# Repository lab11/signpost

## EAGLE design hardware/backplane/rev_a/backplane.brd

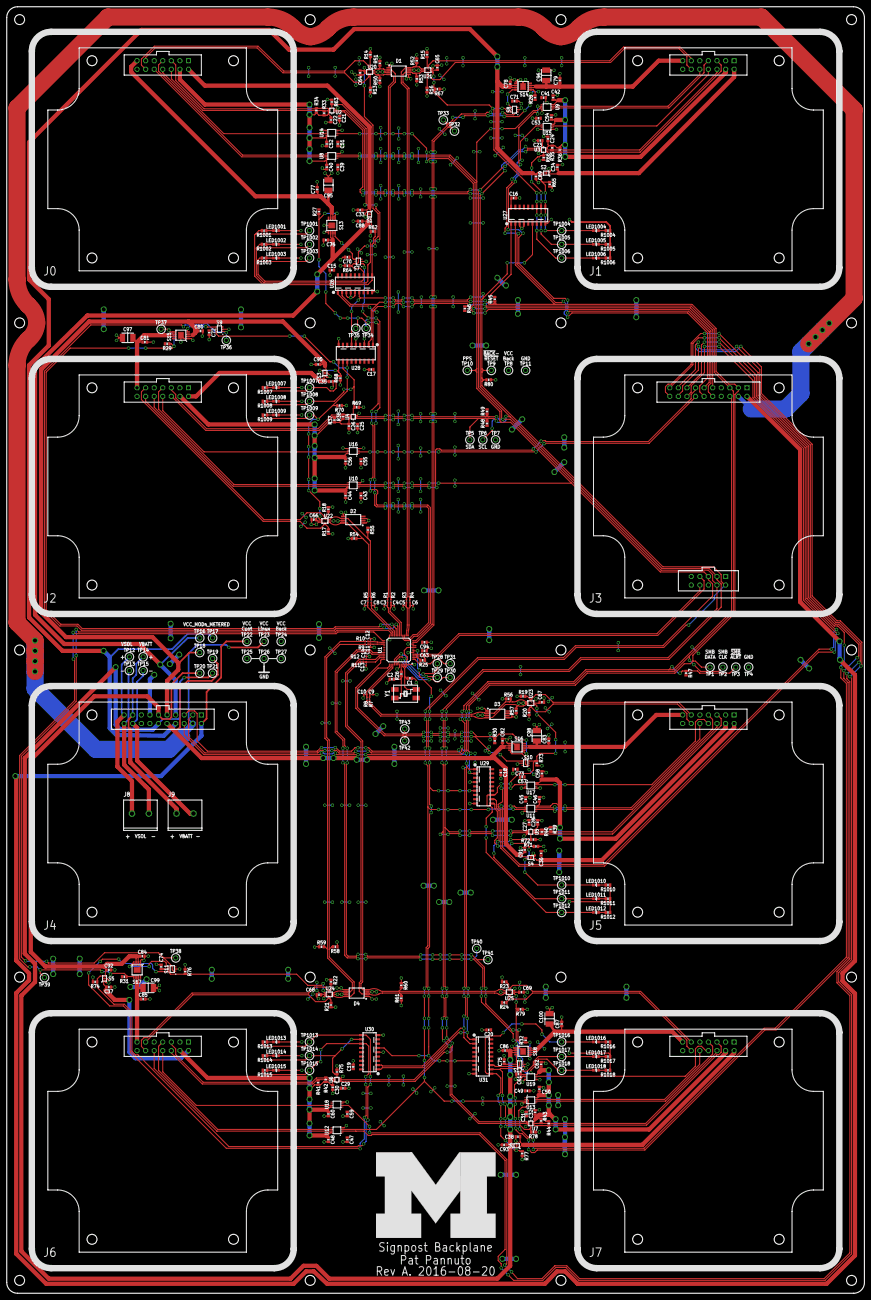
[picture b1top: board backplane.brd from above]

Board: 2 copper layers, 254.0 x 381.0 mm, 342 parts (0 on the bottom side), 193 nets.

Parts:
C1, C2: 22pF, 5% tol; 0603_CAP
C3, C4, C5, C6, C7, C8, C9, C10, C11, C12, C13, C14: 22pF; 0402_CAP
C15, C16, C17, C18, C19, C20, C21, C22, C23, C24, C25, C26, C27, C28, C29, C30, C31, C32, C33, C34, C35, C36, C37, C38, C39, C40, C41, C42, C43, C44, C45, C46, C47, C48, C49, C50, C51, C52, C53, C54, C55, C56, C57, C58, C59, C60, C61, C62, C63, C64, C65, C66, C67, C68, C69, C70, C71, C72, C73, C74, C75, C76, C77, C78, C79, C80, C81, C82, C83, C84, C85, C86, C87: 100nF; 0603_CAP
C88, C89, C90, C91, C92, C93, C94: 4.7uF; 0603_CAP
C95, C96, C97, C98, C99, C100: 150uF; 1210_CAP
D1, D2, D3, D4: SN75240-TSSOP; TSSOP-8
J0, J1, J2, J5, J6, J7: BACKPLANE_GENERIC_MODULE; BACKPLANE_MODULE_14PIN
J3: BACKPLANE_CONTROLLER_MODULE; BACKPLANE_MODULE_20PIN_10PIN
J4: BACKPLANE_POWER_MODULE; BACKPLANE_MODULE_20PIN
J8, J9: SCREW_TERMINAL; PHEONIX-1935161
LED1001, LED1002, LED1003, LED1004, LED1005, LED1006, LED1007, LED1008, LED1009, LED1010, LED1011, LED1012, LED1013, LED1014, LED1015, LED1016, LED1017, LED1018: LED0603; LED-0603
LOGO1: UMICH_SOLID_GIANT; UMICH_SOLID_1000MIL
R1, R2, R3, R4, R5, R6, R7, R8, R9, R10, R11, R12: 27Ω; 0402_RES-HIGH_SPEED
R13, R14, R15, R16, R17, R18, R19, R20, R21, R22, R23, R24: 50Ω; 0603-RES
R25, R26: 1.5kΩ; 0603-RES
R27, R28, R29, R30, R31, R32, R33, R34, R35, R36, R37, R38, R39, R40, R41, R42, R43, R44, R45, R46, R47, R48, R49: 10kΩ; 0603-RES
R50, R51, R52, R53, R54, R55, R56, R57, R58, R59, R60, R61: 15kΩ; 0603-RES
R62, R63, R64, R65, R66, R67, R68, R69, R70, R71, R72, R73, R74, R75, R76, R77, R78, R79, R80: 10MΩ; 0603-RES
R1001, R1002, R1003, R1004, R1005, R1006, R1007, R1008, R1009, R1010, R1011, R1012, R1013, R1014, R1015, R1016, R1017, R1018: 15Ω; 0603-RES
S1, S2, S3, S4, S5, S6: SIP3240X; TDFN4
S7, S8, S9, S10, S11, S12: NC7SZ157; SC70-6
S13, S14, S15, S16, S17, S18: AP2401MP; MSOP-8EP
TP1, TP2, TP3, TP4, TP5, TP6, TP7, TP8, TP9, TP10, TP11, TP12, TP13, TP14, TP15, TP16, TP17, TP18, TP19, TP20, TP21, TP22, TP23, TP24, TP25, TP26, TP27, TP28, TP29, TP30, TP31, TP32, TP33, TP34, TP35, TP36, TP37, TP38, TP39, TP40, TP41, TP42, TP43, TP1001, TP1002, TP1003, TP1004, TP1005, TP1006, TP1007, TP1008, TP1009, TP1010, TP1011, TP1012, TP1013, TP1014, TP1015, TP1016, TP1017, TP1018: TEST_POINT_0.040IN; TESTPOINT_0.040IN
U1: TUSB2077A; LQFP-48
U2, U3, U4, U5, U6, U7: FXMA2102; UMLP-8
U8, U9, U10, U11, U12, U13, U14, U15, U16, U17, U18, U19: SN74LVC2T45; VFSOP-8
U20, U21, U22, U23, U24, U25: TS3USB30E; UQFN-10
U26, U27, U28, U29, U30, U31: MCP23008; SOIC-18
Y1: ABMM

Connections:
!BACKPLANE_RESET: J3.22, R80.2, TP9.TESTPOINT, U1.6, U26.6, U27.6, U28.6, U29.6, U30.6, U31.6
!SMBALERT: J3.6, J4.6, R47.1, TP3.TESTPOINT
CONT_MOD0_IN: J3.9, U8.2
CONT_MOD0_OUT: J3.10, U14.2
CONT_MOD1_IN: J3.11, U9.2
CONT_MOD1_OUT: J3.12, U15.2
CONT_MOD2_IN: J3.13, U10.2
CONT_MOD2_OUT: J3.14, U16.2
CONT_MOD5_IN: J3.15, U11.2
CONT_MOD5_OUT: J3.16, U17.2
CONT_MOD6_IN: J3.17, U12.2
CONT_MOD6_OUT: J3.18, U18.2
CONT_MOD7_IN: J3.19, U13.2
CONT_MOD7_OUT: J3.20, U19.2
CONT_USB+: J3.27, R25.1, U1.3
CONT_USB-: J3.28, U1.4
GND: C1.1, C2.1, C3.2, C4.2, C5.2, C6.2, C7.2, C8.2, C9.2, C10.2, C11.2, C12.2, C13.2, C14.2, C15.2, C16.2, C17.2, C18.2, C19.2, C20.2, C21.2, C22.2, C23.2, C24.2, C25.2, C26.2, C27.2, C28.2, C29.2, C30.2, C31.2, C32.2, C33.2, C34.2, C35.2, C36.2, C37.2, C38.2, C39.2, C40.2, C41.2, C42.2, C43.2, C44.2, C45.2, C46.2, C47.2, C48.2, C49.2, C50.2, C51.2, C52.2, C53.2, C54.2, C55.2, C56.2, C57.2, C58.2, C59.2, C60.2, C61.2, C62.2, C63.1, C64.1, C65.1, C66.1, C67.1, C68.1, C69.1, C70.2, C71.2, C72.2, C73.2, C74.2, C75.2, C76.2, C77.2, C78.2, C79.2, C80.2, C81.2, C82.2, C83.2, C84.2, C85.2, C86.2, C87.2, C88.2, C89.2, C90.2, C91.2, C92.2, C93.2, C94.1, C95.2, C96.2, C97.2, C98.2, C99.2, C100.2, D1.1, D1.3, D1.5, D1.7, D2.1, D2.3, D2.5, D2.7, D3.1, D3.3, D3.5, D3.7, D4.1, D4.3, D4.5, D4.7, J0.1, J0.14, J1.1, J1.14, J2.1, J2.14, J3.1, J3.21, J4.1, J5.1, J5.14, J6.1, J6.14, J7.1, J7.14, LED1001.C, LED1002.C, LED1003.C, LED1007.C, LED1008.C, LED1009.C, LED1013.C, LED1014.C, LED1015.C, R13.2, R14.2, R15.2, R16.2, R17.2, R18.2, R19.2, R20.2, R21.2, R22.2, R23.2, R24.2, R50.1, R51.1, R52.1, R53.1, R54.1, R55.1, R56.1, R57.1, R58.1, R59.1, R60.1, R61.1, R62.1, R63.1, R64.1, R65.1, R66.1, R67.1, R68.1, R69.1, R70.1, R71.1, R72.1, R73.1, R74.1, R75.1, R76.1, R77.1, R78.1, R79.1, R80.1, R1004.1, R1005.1, R1006.1, R1010.1, R1011.1, R1012.1, R1016.1, R1017.1, R1018.1, S1.2, S1.PAD, S2.2, S2.PAD, S3.2, S3.PAD, S4.2, S4.PAD, S5.2, S5.PAD, S6.2, S6.PAD, S7.2, S8.2, S9.2, S10.2, S11.2, S12.2, S13.1, S13.PAD, S14.1, S14.PAD, S15.1, S15.PAD, S16.1, S16.PAD, S17.1, S17.PAD, S18.1, S18.PAD, TP4.TESTPOINT, TP7.TESTPOINT, TP11.TESTPOINT, TP25.TESTPOINT, TP26.TESTPOINT, TP27.TESTPOINT, U1.5, U1.10, U1.24, U1.43, U1.48, U2.4, U3.4, U4.4, U5.4, U6.4, U7.4, U8.4, U9.4, U10.4, U11.4, U12.4, U13.4, U14.4, U14.5, U15.4, U15.5, U16.4, U16.5, U17.4, U17.5, U18.4, U19.4, U19.5, U20.4, U20.10, U21.4, U21.10, U22.4, U22.10, U23.4, U23.10, U24.4, U24.10, U25.4, U25.10, U26.3, U26.4, U26.5, U26.9, U27.3, U27.4, U27.9, U28.3, U28.5, U28.9, U29.4, U29.9, U30.5, U30.9, U31.9
HUB_!OVRCUR1: R28.1, S14.5, TP33.TESTPOINT, U1.12
HUB_!OVRCUR2: R27.1, S13.5, TP35.TESTPOINT, U1.16
HUB_!OVRCUR3: R29.1, S15.5, TP37.TESTPOINT, U1.20
HUB_!OVRCUR4: R31.1, S17.5, TP39.TESTPOINT, U1.25
HUB_!OVRCUR6: R32.1, S18.5, TP41.TESTPOINT, U1.33
HUB_!OVRCUR7: R30.1, S16.5, TP43.TESTPOINT, U1.37
HUB_!PWRON1: S8.1, TP32.TESTPOINT, U1.11
HUB_!PWRON2: S7.1, TP34.TESTPOINT, U1.15
HUB_!PWRON3: S9.1, TP36.TESTPOINT, U1.19
HUB_!PWRON4: S11.1, TP38.TESTPOINT, U1.23
HUB_!PWRON6: S12.1, TP40.TESTPOINT, U1.32
HUB_!PWRON7: S10.1, TP42.TESTPOINT, U1.36
HUB_CFG: TP28.TESTPOINT, U1.40
HUB_DM1: C6.1, R4.1, U1.13
HUB_DM2: C4.1, R2.1, U1.17
HUB_DM3: C8.1, R6.1, U1.21
HUB_DM4: C12.1, R10.1, U1.26
HUB_DM6: C14.1, R12.1, U1.34
HUB_DM7: C10.1, R8.1, U1.38
HUB_DP1: C5.1, R3.1, U1.14
HUB_DP2: C3.1, R1.1, U1.18
HUB_DP3: C7.1, R5.1, U1.22
HUB_DP4: C11.1, R9.1, U1.27
HUB_DP6: C13.1, R11.1, U1.35
HUB_DP7: C9.1, R7.1, U1.39
HUB_PORTDIS: TP30.TESTPOINT, U1.42
HUB_PORTPWR: TP29.TESTPOINT, U1.41
MOD0_5V: C33.1, J0.2, S1.1
MOD0_5V_METERED: C76.1, C88.1, J4.7, S1.3, S13.2, S13.3, TP16.TESTPOINT
MOD0_D+_HUB-SW: D1.4, R1.2, R50.2, U20.3
MOD0_D-_HUB-SW: D1.2, R2.2, R51.2, U20.5
MOD0_IN: J0.10, U8.7
MOD0_ISO_I2C: R63.2, R1002.2, TP1002.TESTPOINT, U2.5, U26.11
MOD0_ISO_POWER: R62.2, R1001.2, S1.4, TP1001.TESTPOINT, U26.10
MOD0_ISO_USB: R64.2, R1003.2, S7.6, TP1003.TESTPOINT, U20.8, U26.12
MOD0_OUT: J0.8, U14.7
MOD0_PPS: J0.7, U8.6
MOD0_SCL: J0.5, R34.2, U2.6
MOD0_SDA: J0.6, R33.2, U2.7
MOD0_USB+: J0.11, U20.1
MOD0_USB-: J0.12, U20.7
MOD0_USB_!EN: S7.4, S13.4
MOD0_USB_VBUS: C77.1, C95.1, J0.13, S13.6, S13.7
MOD0_VCCIO: C22.1, C40.1, C52.1, J0.4, R33.1, R34.1, U2.8, U8.8, U14.8
MOD1_5V: C34.1, J1.2, S2.1
MOD1_5V_METERED: C78.1, C89.1, J4.8, S2.3, S14.2, S14.3, TP17.TESTPOINT
MOD1_D+_HUB-SW: D1.8, R3.2, R52.2, U21.3
MOD1_D-_HUB-SW: D1.6, R4.2, R53.2, U21.5
MOD1_IN: J1.10, U9.7
MOD1_ISO_I2C: LED1005.A, R66.2, TP1005.TESTPOINT, U3.5, U27.11
MOD1_ISO_POWER: LED1004.A, R65.2, S2.4, TP1004.TESTPOINT, U27.10
MOD1_ISO_USB: LED1006.A, R67.2, S8.6, TP1006.TESTPOINT, U21.8, U27.12
MOD1_OUT: J1.8, U15.7
MOD1_PPS: J1.7, U9.6
MOD1_SCL: J1.5, R36.2, U3.6
MOD1_SDA: J1.6, R35.2, U3.7
MOD1_USB+: J1.11, U21.1
MOD1_USB-: J1.12, U21.7
MOD1_USB_!EN: S8.4, S14.4
MOD1_USB_VBUS: C79.1, C96.1, J1.13, S14.6, S14.7
MOD1_VCCIO: C24.1, C42.1, C54.1, J1.4, R35.1, R36.1, U3.8, U9.8, U15.8
MOD2_5V: C35.1, J2.2, S3.1
MOD2_5V_METERED: C80.1, C90.1, J4.9, S3.3, S15.2, S15.3, TP18.TESTPOINT
MOD2_D+_HUB-SW: D2.8, R5.2, R54.2, U22.3
MOD2_D-_HUB-SW: D2.6, R6.2, R55.2, U22.5
MOD2_IN: J2.10, U10.7
MOD2_ISO_I2C: R69.2, R1008.2, TP1008.TESTPOINT, U4.5, U28.11
MOD2_ISO_POWER: R68.2, R1007.2, S3.4, TP1007.TESTPOINT, U28.10
MOD2_ISO_USB: R70.2, R1009.2, S9.6, TP1009.TESTPOINT, U22.8, U28.12
MOD2_OUT: J2.8, U16.7
MOD2_PPS: J2.7, U10.6
MOD2_SCL: J2.5, R38.2, U4.6
MOD2_SDA: J2.6, R37.2, U4.7
MOD2_USB+: J2.11, U22.1
MOD2_USB-: J2.12, U22.7
MOD2_USB_!EN: S9.4, S15.4
MOD2_USB_VBUS: C81.1, C97.1, J2.13, S15.6, S15.7
MOD2_VCCIO: C26.1, C44.1, C56.1, J2.4, R37.1, R38.1, U4.8, U10.8, U16.8
MOD5_5V: C36.1, J5.2, S4.1
MOD5_5V_METERED: C82.1, C91.1, J4.10, S4.3, S16.2, S16.3, TP19.TESTPOINT
MOD5_D+_HUB-SW: D3.2, R7.2, R56.2, U23.3
MOD5_D-_HUB-SW: D3.4, R8.2, R57.2, U23.5
MOD5_IN: J5.10, U11.7
MOD5_ISO_I2C: LED1011.A, R72.2, TP1011.TESTPOINT, U5.5, U29.11
MOD5_ISO_POWER: LED1010.A, R71.2, S4.4, TP1010.TESTPOINT, U29.10
MOD5_ISO_USB: LED1012.A, R73.2, S10.6, TP1012.TESTPOINT, U23.8, U29.12
MOD5_OUT: J5.8, U17.7
MOD5_PPS: J5.7, U11.6
MOD5_SCL: J5.5, R40.2, U5.6
MOD5_SDA: J5.6, R39.2, U5.7
MOD5_USB+: J5.11, U23.1
MOD5_USB-: J5.12, U23.7
MOD5_USB_!EN: S10.4, S16.4
MOD5_USB_VBUS: C83.1, C98.1, J5.13, S16.6, S16.7
MOD5_VCCIO: C28.1, C46.1, C58.1, J5.4, R39.1, R40.1, U5.8, U11.8, U17.8
MOD6_5V: C37.1, J6.2, S5.1
MOD6_5V_METERED: C84.1, C92.1, J4.11, S5.3, S17.2, S17.3, TP20.TESTPOINT
MOD6_D+_HUB-SW: D4.8, R9.2, R58.2, U24.3
MOD6_D-_HUB-SW: D4.6, R10.2, R59.2, U24.5
MOD6_IN: J6.10, U12.7
MOD6_ISO_I2C: R75.2, R1014.2, TP1014.TESTPOINT, U6.5, U30.11
MOD6_ISO_POWER: R74.2, R1013.2, S5.4, TP1013.TESTPOINT, U30.10
MOD6_ISO_USB: R76.2, R1015.2, S11.6, TP1015.TESTPOINT, U24.8, U30.12
MOD6_OUT: J6.8, U18.7
MOD6_PPS: J6.7, U12.6
MOD6_SCL: J6.5, R42.2, U6.6
MOD6_SDA: J6.6, R41.2, U6.7
MOD6_USB+: J6.11, U24.1
MOD6_USB-: J6.12, U24.7
MOD6_USB_!EN: S11.4, S17.4
MOD6_USB_VBUS: C85.1, C99.1, J6.13, S17.6, S17.7
MOD6_VCCIO: C30.1, C48.1, C60.1, J6.4, R41.1, R42.1, U6.8, U12.8, U18.8
MOD7_5V: C38.1, J7.2, S6.1
MOD7_5V_METERED: C86.1, C93.1, J4.12, S6.3, S18.2, S18.3, TP21.TESTPOINT
MOD7_D+_HUB-SW: D4.4, R11.2, R60.2, U25.3
MOD7_D-_HUB-SW: D4.2, R12.2, R61.2, U25.5
MOD7_IN: J7.10, U13.7
MOD7_ISO_I2C: LED1017.A, R78.2, TP1017.TESTPOINT, U7.5, U31.11
MOD7_ISO_POWER: LED1016.A, R77.2, S6.4, TP1016.TESTPOINT, U31.10
MOD7_ISO_USB: LED1018.A, R79.2, S12.6, TP1018.TESTPOINT, U25.8, U31.12
MOD7_OUT: J7.8, U19.7
MOD7_PPS: J7.7, U13.6
MOD7_SCL: J7.5, R44.2, U7.6
MOD7_SDA: J7.6, R43.2, U7.7
MOD7_USB+: J7.11, U25.1
MOD7_USB-: J7.12, U25.7
MOD7_USB_!EN: S12.4, S18.4
MOD7_USB_VBUS: C87.1, C100.1, J7.13, S18.6, S18.7
MOD7_VCCIO: C32.1, C50.1, C62.1, J7.4, R43.1, R44.1, U7.8, U13.8, U19.8
MOD_SCL: J3.24, R49.1, TP6.TESTPOINT, U2.3, U3.3, U4.3, U5.3, U6.3, U7.3
MOD_SDA: J3.23, R48.1, TP5.TESTPOINT, U2.2, U3.2, U4.2, U5.2, U6.2, U7.2
unnamed: LED1001.A, R1001.1
unnamed: LED1002.A, R1002.1
unnamed: LED1003.A, R1003.1
unnamed: LED1007.A, R1007.1
unnamed: LED1008.A, R1008.1
unnamed: LED1009.A, R1009.1
unnamed: LED1013.A, R1013.1
unnamed: LED1014.A, R1014.1
unnamed: LED1015.A, R1015.1
unnamed: LED1004.C, R1004.2
unnamed: LED1005.C, R1005.2
unnamed: R25.2, U1.2
unnamed: LED1006.C, R1006.2
unnamed: C2.2, R26.1, Y1.1
unnamed: LED1010.C, R1010.2
unnamed: LED1011.C, R1011.2
unnamed: R13.1, U20.2
unnamed: R24.1, U25.6
unnamed: R23.1, U25.2
unnamed: R22.1, U24.6
unnamed: R21.1, U24.2
unnamed: R20.1, U23.6
unnamed: R19.1, U23.2
unnamed: R17.1, U22.2
unnamed: R18.1, U22.6
unnamed: R16.1, U21.6
unnamed: R15.1, U21.2
unnamed: LED1012.C, R1012.2
unnamed: LED1016.C, R1016.2
unnamed: LED1017.C, R1017.2
unnamed: R14.1, U20.6
unnamed: LED1018.C, R1018.2
unnamed: C1.2, U1.45, Y1.3
unnamed: R26.2, U1.44
PPS: J3.25, TP10.TESTPOINT, U8.3, U9.3, U10.3, U11.3, U12.3, U13.3
SMBCLK: J3.5, J4.5, R46.1, TP2.TESTPOINT, U26.1, U27.1, U28.1, U29.1, U30.1, U31.1
SMBDATA: J3.3, J4.3, R45.1, TP1.TESTPOINT, U26.2, U27.2, U28.2, U29.2, U30.2, U31.2
USB_SUSPEND_STATUS: TP31.TESTPOINT, U1.1
VBATT+: J4.17, J9.1, TP14.TESTPOINT
VBATT-: J4.18, J9.2, TP15.TESTPOINT
VCC_BACKPLANE: C15.1, C16.1, C17.1, C18.1, C19.1, C20.1, C21.1, C23.1, C25.1, C27.1, C29.1, C31.1, C39.1, C41.1, C43.1, C45.1, C47.1, C49.1, C51.1, C53.1, C55.1, C57.1, C59.1, C61.1, C63.2, C64.2, C65.2, C66.2, C67.2, C68.2, C69.2, C70.1, C71.1, C72.1, C73.1, C74.1, C75.1, C94.2, J4.13, R27.2, R28.2, R29.2, R30.2, R31.2, R32.2, R45.2, R46.2, R47.2, R48.2, R49.2, S7.3, S7.5, S8.3, S8.5, S9.3, S9.5, S10.3, S10.5, S11.3, S11.5, S12.3, S12.5, TP8.TESTPOINT, TP24.TESTPOINT, U1.8, U1.9, U1.46, U1.47, U2.1, U3.1, U4.1, U5.1, U6.1, U7.1, U8.1, U8.5, U9.1, U9.5, U10.1, U10.5, U11.1, U11.5, U12.1, U12.5, U13.1, U13.5, U14.1, U15.1, U16.1, U17.1, U18.1, U19.1, U20.9, U21.9, U22.9, U23.9, U24.9, U25.9, U26.18, U27.5, U27.18, U28.4, U28.18, U29.3, U29.5, U29.18, U30.3, U30.4, U30.18, U31.3, U31.4, U31.5, U31.18
VCC_CONTROLLER: J3.2, J4.2, TP22.TESTPOINT
VCC_LINUX: J3.4, J4.4, TP23.TESTPOINT
VSOL+: J4.19, J8.1, TP12.TESTPOINT
VSOL-: J4.20, J8.2, TP13.TESTPOINT

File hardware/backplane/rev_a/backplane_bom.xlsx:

Qty | Value | Device | Package | Parts | Description | DIGIKEY
2 | 22pF, 5% tol | CAPACITOR0603_CAP | 0603_CAP | C1, C2 | 0402 Capacitor | 1276-1023-1-ND
12 | 22pF | CAPACITOR0402_CAP | 0402_CAP | C3, C4, C5, C6, C7, C8, C9, C10, C11, C12, C13, C14 | 0402 Capacitor | 490-5868-1-ND
73 | 100nF | CAPACITOR0603_CAP | 0603_CAP | C15, C16, C17, C18, C19, C20, C21, C22, C23, C24, C25, C26, C27, C28, C29, C30,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 | 0402 Capacitor | 490-1524-1-ND
7 | 4.7uF | CAPACITOR0603_CAP | 0603_CAP | C88, C89, C90, C91, C92, C93, C94 | 0402 Capacitor
6 | 150uF | CAPACITOR1210_CAP | 1210_CAP | C95, C96, C97, C98, C99, C100 | 0402 Capacitor | 1276-3367-1-ND
4 | SN75240-TSSOP | SN75240-TSSOP | TSSOP-8 | D1, D2, D3, D4 | TVS Diodes [suggested for TI USB Hub] (2 array) | 296-6596-1-ND
6 | BACKPLANE_GENERIC_MODULE | BACKPLANE_GENERIC_MODULE | BACKPLANE_MODULE_14PIN | J0, J1, J2, J5, J6, J7 | Signpost generic module recepticle | S9195-ND
1 | BACKPLANE_CONTROLLER_MODULE | BACKPLANE_CONTROLLER_MODULE | BACKPLANE_MODULE_20PIN_10PIN | J3 | Signpost controller recepticle | S9197-ND , S9194-ND
1 | BACKPLANE_POWER_MODULE | BACKPLANE_POWER_MODULE | BACKPLANE_MODULE_20PIN | J4 | Signpost power module recepticle | S9197-ND
2 | SCREW_TERMINAL | SCREW_TERMINAL | PHEONIX-1935161 | J8, J9 | PCB terminal block 5mm | 277-1667-ND
18 | LED0603 | LED0603 | LED-0603 | LED1001, LED1002, LED1003, LED1004, LED1005, LED1006, LED1007, LED1008, LED1009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 | LED
12 | 27 | RESISTOR0402_RES-HIGH_SPEED | 0402_RES-HIGH_SPEED | R1, R2, R3, R4, R5, R6, R7, R8, R9, R10, R11, R12 | Resistor
12 | 50 | RESISTOR0603_RES | 0603-RES | R13, R14, R15, R16, R17, R18, R19, R20, R21, R22, R23, R24 | Resistor
2 | 1.5k | RESISTOR0603_RES | 0603-RES | R25, R26 | Resistor
23 | 10k | RESISTOR0603_RES | 0603-RES | R27, R28, R29, R30, R31, R32, R33, R34, R35, R36, R37, R38, R39, R40, R41, R42,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 | Resistor
12 | 15k | RESISTOR0603_RES | 0603-RES | R50, R51, R52, R53, R54, R55, R56, R57, R58, R59, R60, R61 | Resistor
19 | 10M | RESISTOR0603_RES | 0603-RES | R62, R63, R64, R65, R66, R67, R68, R69, R70, R71, R72, R73, R74, R75, R76, R77,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 | Resistor
18 | 15 | RESISTOR0603_RES | 0603-RES | R1001, R1002, R1003, R1004, R1005, R1006, R1007, R1008, R1009, R1010, R1011, R1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 | Resistor
6 | SIP3240X | SIP3240X | TDFN4 | S1, S2, S3, S4, S5, S6 | High power (2.4 A) high-side switch | SIP32402ADNP-T1GE4CT-ND
6 | AP2401MP | AP2401MP | MSOP-8EP | S13, S14, S15, S16, S17, S18 | USB Power Switch | AP2401MP-13DICT-ND
6 | NC7SZ157 | NC7SZ157 | SC70-6 | S7, S8, S9, S10, S11, S12 | MUX | NC7SZ157P6XCT-ND
61 | TEST_POINT_0.040IN | TEST_POINT_0.040IN | TESTPOINT_0.040IN | TP1, TP2, TP3, TP4, TP5, TP6, TP7, TP8, TP9, TP10, TP11, TP12, TP13, TP14, TP15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 | 0.040in Test Point | 5001K-ND
1 | TUSB2077A | TUSB2077A | LQFP-48 | U1 | Full Speed USB Hub - 7 Port | 296-37871-1-ND
6 | FXMA2102 | FXMA2102 | UMLP-8 | U2, U3, U4, U5, U6, U7 | Dual Supply, 2-Bit Voltage Translator / Buffer / Repeater / Isolator for I2C | FXMA2102UMXCT-ND
6 | TS3USB30E | TS3USB30E | UQFN-10 | U20, U21, U22, U23, U24, U25 | USB Mux with OE control and ESD | 296-24684-1-ND
6 | MCP23008 | MCP23008 | SOIC-18 | U26, U27, U28, U29, U30, U31 | GPIO Extender via I2C - 8 Pin | MCP23008T-E/SOCT-ND
12 | SN74LVC2T45 | SN74LVC2T45 | VFSOP-8 | U8, U9, U10, U11, U12, U13, U14, U15, U16, U17, U18, U19 | Bidirectional Buffer / Level Converter 2 Circuits | 296-17014-1-ND
1 | ABMM | ABMM | ABMM | Y1 | Low-Profile SMD crystal | 535-10156-1-ND

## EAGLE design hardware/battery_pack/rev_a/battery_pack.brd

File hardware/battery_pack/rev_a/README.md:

This is a first pass at a signpost battery pack.

It will be simple. Several li-ion cells with a protection IC.

I would like to have OV/UV/OT/UT protection.

In the future we may consider adding active temperature
compensation (such as a pcb heater under the batteries),
but this design will not include that feature.

I am planning on using the TIbq77904. This will protect
series li-ion cells. It will not balance them (and could 
therefore not get optimal pack lifetime) but it is a 
relatively simple first pass.

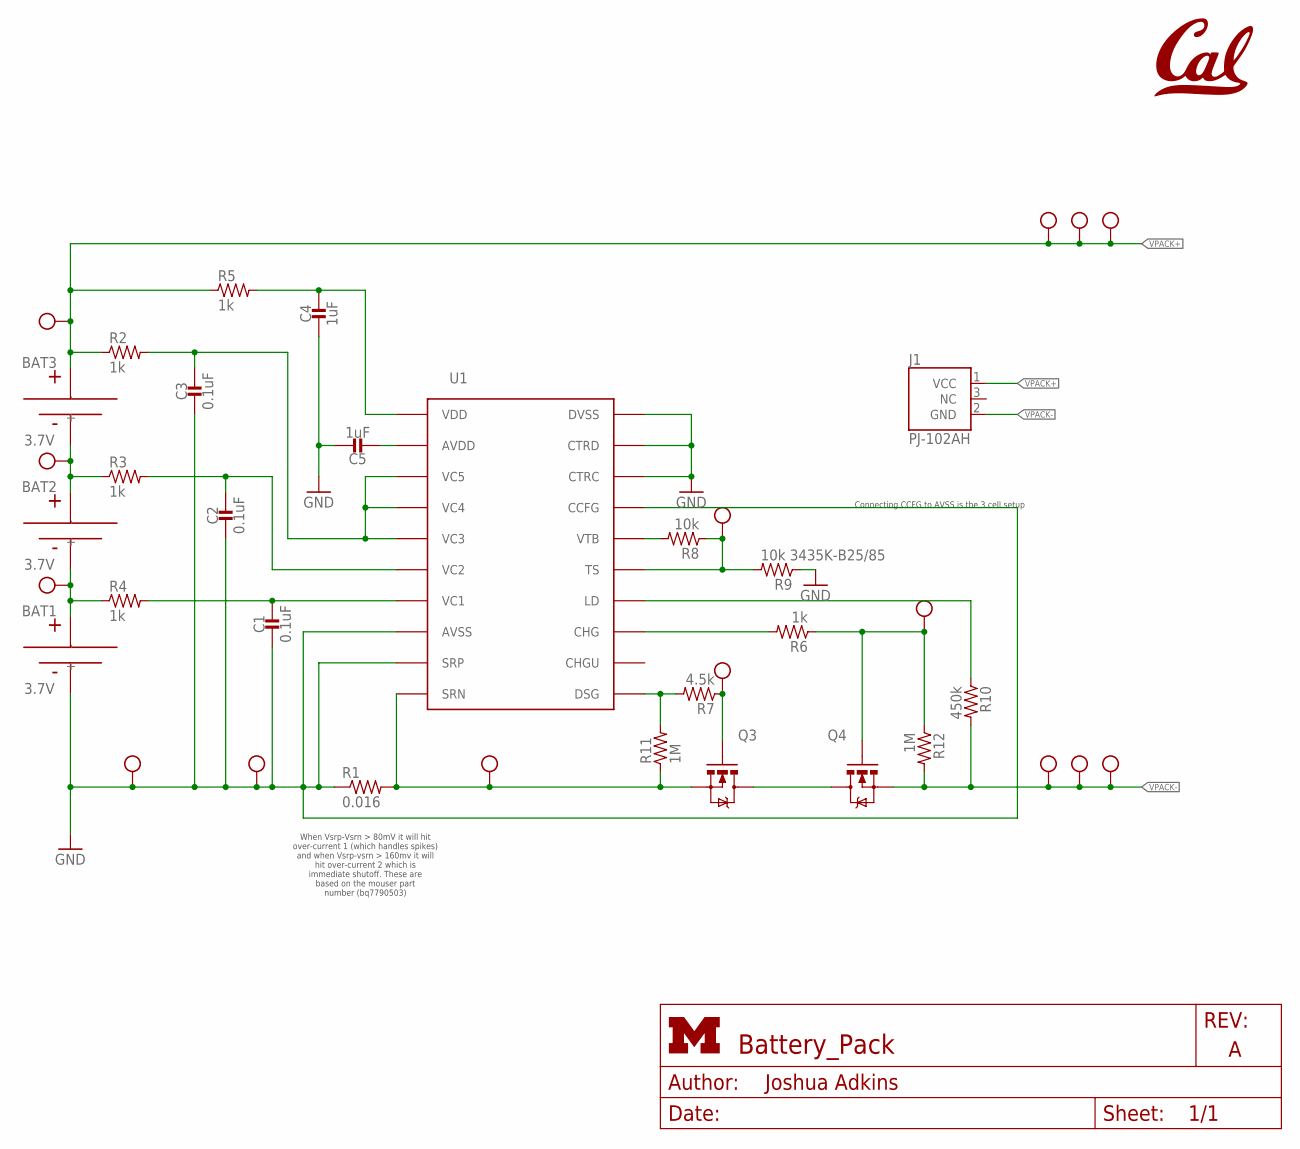
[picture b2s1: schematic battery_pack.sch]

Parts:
BAT1, BAT2, BAT3: 3.7V; PL-809797-1C
C1, C2, C3: 0.1uF; 0603_CAP
C4, C5: 1uF; 0603_CAP
J1: PJ-102AH
Q3, Q4: MOSFET-NCHANNELFDD8580; DPAK
R1: 0.016; R1206
R2, R3, R4, R5, R6: 1k; 0603-RES
R7: 4.5k; 0603-RES
R8: 10k; 0603-RES
R9: 10k 3435K-B25/85; 0603-RES
R10: 450k; 0603-RES
R11, R12: 1M; 0603-RES
TP1, TP2, TP5, TP6, TP7, TP8, TP14, TP15: TEST_POINT_0.112IN; TESTPOINT_0.112IN
TP3, TP4, TP9, TP10, TP11, TP12, TP13: TEST_POINT_0.040IN; TESTPOINT_0.040IN
U1: BQ77904; TSSOP-20/6MM
U$1: UCB_CAL500MIL; UCB_CAL_500MIL

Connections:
GND: BAT1.-, C1.2, C2.2, C3.2, C4.2, C5.1, R1.1, R9.1, TP7.1, TP9.TESTPOINT, U1.8 (AVSS), U1.9 (SRP), U1.17 (CCFG), U1.18 (CTRC), U1.19 (CTRD), U1.20 (DVSS)
unnamed: BAT1.+, BAT2.-, R4.1, TP15.1
unnamed: BAT2.+, BAT3.-, R3.1, TP14.1
unnamed: C1.1, R4.2, U1.7 (VC1)
unnamed: C2.1, R3.2, U1.6 (VC2)
unnamed: C3.1, R2.2, U1.3 (VC5), U1.4 (VC4), U1.5 (VC3)
unnamed: Q3.4 (D), Q4.4 (D)
unnamed: Q3.3 (S), R1.2, R11.1, TP10.TESTPOINT, U1.10 (SRN)
unnamed: C4.1, R5.2, U1.1 (VDD)
unnamed: R7.2, R11.2, U1.11 (DSG)
unnamed: C5.2, U1.2 (AVDD)
unnamed: Q3.1 (G), R7.1, TP11.TESTPOINT
unnamed: R6.2, U1.13 (CHG)
unnamed: Q4.1 (G), R6.1, R12.1, TP12.TESTPOINT
unnamed: R10.1, U1.14 (LD)
unnamed: R8.2, U1.16 (VTB)
unnamed: R8.1, R9.2, TP13.TESTPOINT, U1.15 (TS)
VPACK+: BAT3.+, J1.1 (VCC), R2.1, R5.1, TP1.1, TP3.TESTPOINT, TP6.1, TP8.1
VPACK-: J1.2 (GND), Q4.3 (S), R10.2, R12.2, TP2.1, TP4.TESTPOINT, TP5.1

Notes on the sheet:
Connecting CCFG to AVSS is the 3 cell setup
When Vsrp-Vsrn > 80mV it will hit over-current 1 (which handles spikes) and when Vsrp-vsrn > 160mv it will hit over-current 2 which is immediate shutoff. These are based on the mouser part number (bq7790503)

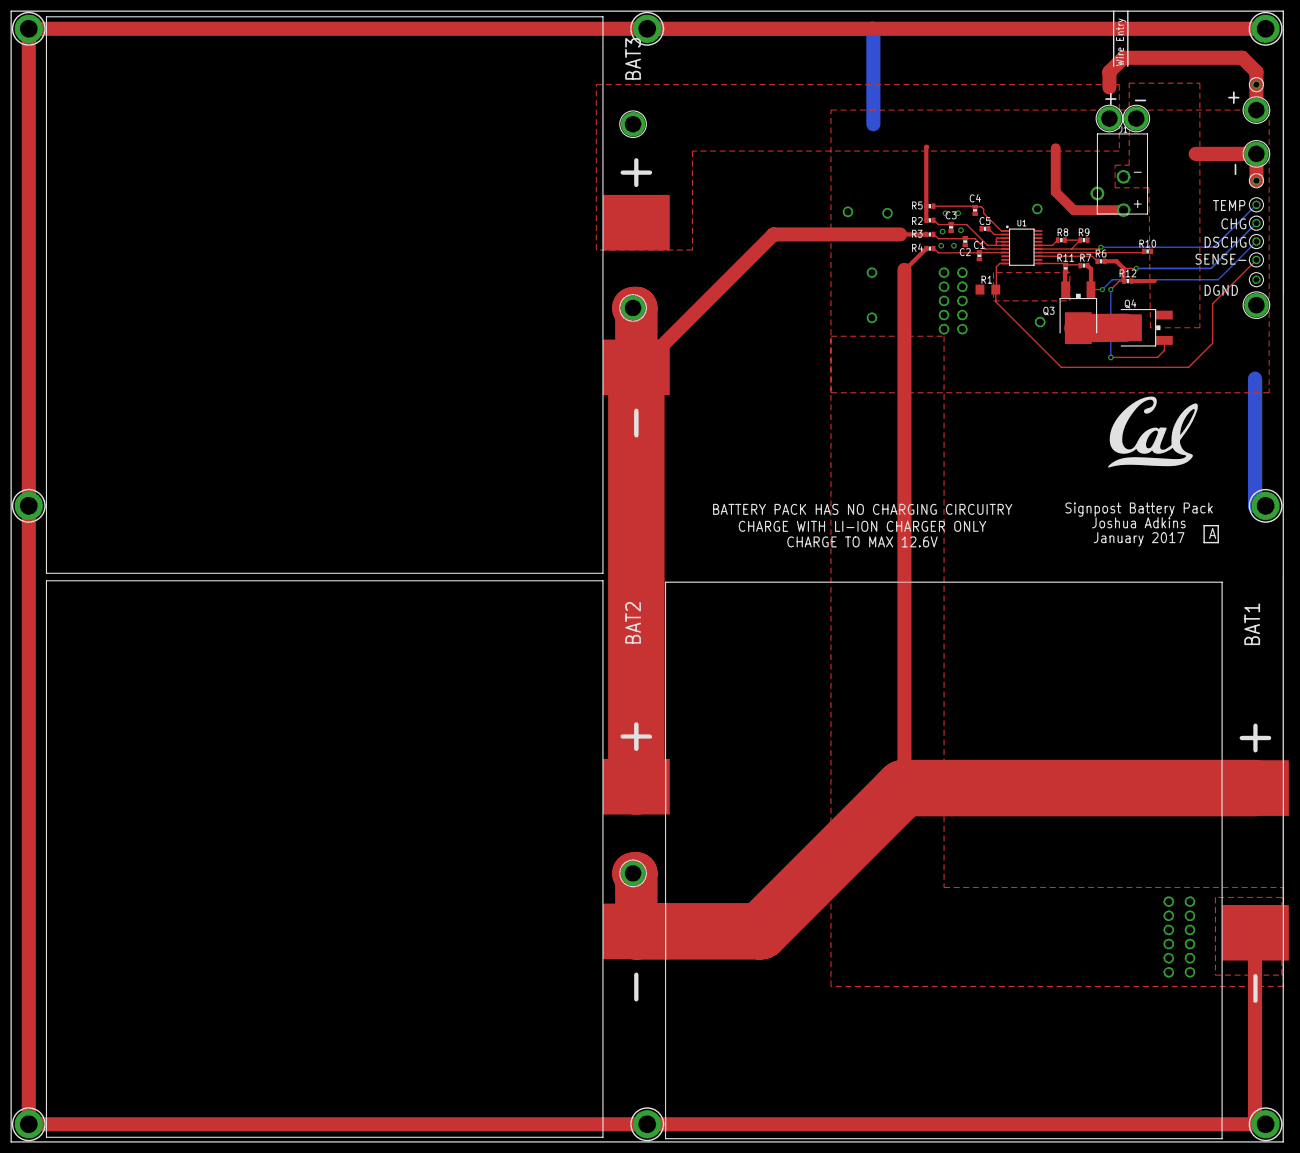
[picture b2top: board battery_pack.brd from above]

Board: 2 copper layers, 228.6 x 203.2 mm, 40 parts (0 on the bottom side), 19 nets.

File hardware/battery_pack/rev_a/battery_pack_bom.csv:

"# Bill of Materials",,,,,,,
"# Converted from battery_pack_bom.xlsx",,,,,,,
"# Generated by bom_to_text.py",,,,,,,
"#",,,,,,,
Part,Value,Device,Package,Description,DIGIKEY,MOUSER,NEWARK
BAT1,3.7V,BAT-CELL,PL-809797-1C,A single cell of a battery,,,
BAT2,3.7V,BAT-CELL,PL-809797-1C,A single cell of a battery,,,
BAT3,3.7V,BAT-CELL,PL-809797-1C,A single cell of a battery,,,
C1,0.1uF,CAPACITOR0603_CAP,0603_CAP,0402 Capacitor,311-1087-1-ND,,
C2,0.1uF,CAPACITOR0603_CAP,0603_CAP,0402 Capacitor,311-1087-1-ND,,
C3,0.1uF,CAPACITOR0603_CAP,0603_CAP,0402 Capacitor,311-1087-1-ND,,
C4,1uF,CAPACITOR0603_CAP,0603_CAP,0402 Capacitor,311-1445-1-ND,,
C5,1uF,CAPACITOR0603_CAP,0603_CAP,0402 Capacitor,311-1445-1-ND,,
J1,PJ-102AH,PJ-102AH,PJ-102AH,DC Power Jack,CP-102AH-ND,,
Q1,MOSFET-NCHANNELFDD8580,MOSFET-NCHANNELFDD8580,DPAK,Generic NMOS footprint,FDD8447L_F085CT-ND,,
Q2,MOSFET-NCHANNELFDD8580,MOSFET-NCHANNELFDD8580,DPAK,Generic NMOS footprint,FDD8447L_F085CT-ND,,
R1,0.016,R-US_R1206,R1206,"RESISTOR, American symbol",P0.016BVCT-ND,,
R2,1k,RESISTOR0603_RES,0603-RES,Resistor,311-1.0KGRCT-ND,,
R3,1k,RESISTOR0603_RES,0603-RES,Resistor,311-1.0KGRCT-ND,,
R4,1k,RESISTOR0603_RES,0603-RES,Resistor,311-1.0KGRCT-ND,,
R5,1k,RESISTOR0603_RES,0603-RES,Resistor,311-1.0KGRCT-ND,,
R6,1k,RESISTOR0603_RES,0603-RES,Resistor,311-1.0KGRCT-ND,,
R7,4.5k,RESISTOR0603_RES,0603-RES,Resistor,311-4.53KHRCT-ND,,
R8,10k,RESISTOR0603_RES,0603-RES,Resistor,311-10KGRCT-ND,,
R9,10k 3435K-B25/85 ,RESISTOR0603_RES,0603-RES,Resistor,445-2554-1-ND,,
R10,450k,RESISTOR0603_RES,0603-RES,Resistor,311-453KHRCT-ND,,
R11,1M,RESISTOR0603_RES,0603-RES,Resistor,311-1.0MGRCT-ND,,
R12,1M,RESISTOR0603_RES,0603-RES,Resistor,311-1.0MGRCT-ND,,
TP1,TEST_POINT_0.112IN,TEST_POINT_0.112IN,TESTPOINT_0.112IN,"Solder terminal, turreted",,,40F6015
TP2,TEST_POINT_0.112IN,TEST_POINT_0.112IN,TESTPOINT_0.112IN,"Solder terminal, turreted",,,40F6015
TP3,TEST_POINT_0.040IN,TEST_POINT_0.040IN,TESTPOINT_0.040IN,0.040in Test Point,5001K-ND,,
TP4,TEST_POINT_0.040IN,TEST_POINT_0.040IN,TESTPOINT_0.040IN,0.040in Test Point,5001K-ND,,
TP5,TEST_POINT_0.112IN,TEST_POINT_0.112IN,TESTPOINT_0.112IN,"Solder terminal, turreted",,,40F6015
TP6,TEST_POINT_0.112IN,TEST_POINT_0.112IN,TESTPOINT_0.112IN,"Solder terminal, turreted",,,40F6015
TP7,TEST_POINT_0.112IN,TEST_POINT_0.112IN,TESTPOINT_0.112IN,"Solder terminal, turreted",,,40F6015
TP8,TEST_POINT_0.112IN,TEST_POINT_0.112IN,TESTPOINT_0.112IN,"Solder terminal, turreted",,,40F6015
TP9,TEST_POINT_0.040IN,TEST_POINT_0.040IN,TESTPOINT_0.040IN,0.040in Test Point,5001K-ND,,
TP10,TEST_POINT_0.040IN,TEST_POINT_0.040IN,TESTPOINT_0.040IN,0.040in Test Point,5001K-ND,,
TP11,TEST_POINT_0.040IN,TEST_POINT_0.040IN,TESTPOINT_0.040IN,0.040in Test Point,5001K-ND,,
TP12,TEST_POINT_0.040IN,TEST_POINT_0.040IN,TESTPOINT_0.040IN,0.040in Test Point,5001K-ND,,
TP13,TEST_POINT_0.040IN,TEST_POINT_0.040IN,TESTPOINT_0.040IN,0.040in Test Point,5001K-ND,,
TP14,TEST_POINT_0.112IN,TEST_POINT_0.112IN,TESTPOINT_0.112IN,"Solder terminal, turreted",,,40F6015
TP15,TEST_POINT_0.112IN,TEST_POINT_0.112IN,TESTPOINT_0.112IN,"Solder terminal, turreted",,,40F6015
U1,BQ77904,BQ77904,TSSOP-20/6MM,A battery protection chip with OV/UV/OT/UT,296-44599-5-ND,595-BQ7790503PW,

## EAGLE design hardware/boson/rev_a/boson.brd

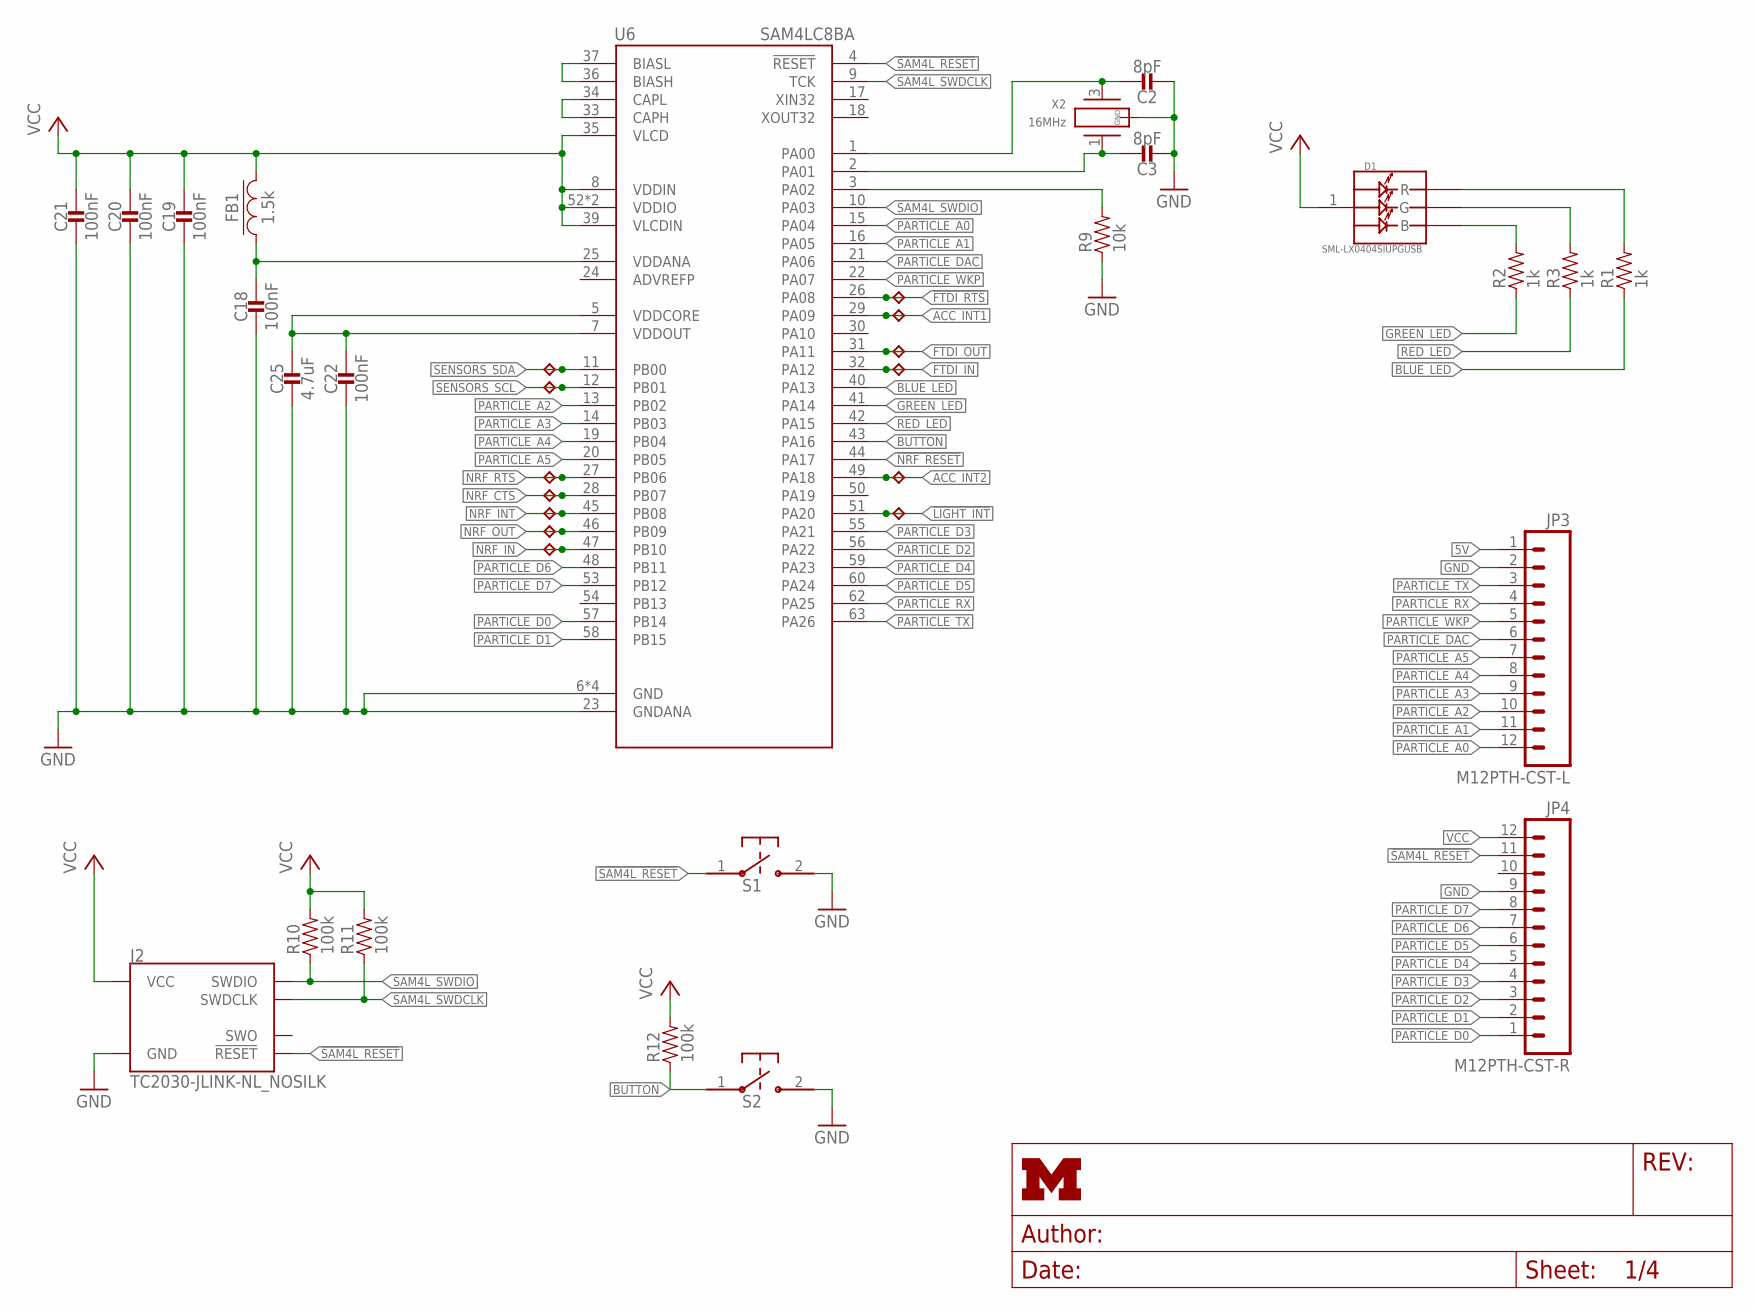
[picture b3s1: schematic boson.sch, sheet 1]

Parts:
C2, C3: 8pF; 0402_CAP; DIGIKEY 490-8230-1-ND
C18, C19, C20, C21, C22: 100nF; 0402_CAP; DIGIKEY 490-10777-1-ND
C25: 4.7uF; 0402_CAP; DIGIKEY 490-13252-1-ND
D1: SML-LX0404SIUPGUSB; 1MM_SQ_4PAD
FB1: 1.5k; 0402_CAP; DIGIKEY 490-5216-1-ND
J2: TC2030-JLINK-NL_NOSILK; TC2030-IDC-NL_NOSILK
JP3: M12PTH-CST-L; 1X12-CASTELLATED
JP4: M12PTH-CST-R; 1X12-CASTELLATED
R1, R2, R3: 1k; 0402_RES
R9: 10k; 0402_RES; DIGIKEY 1276-3431-1-ND
R10, R11, R12: 100k; 0402_RES; DIGIKEY 1276-3432-1-ND
S1, S2: B3U-1000P
TP1, TP2, TP3, TP4, TP5, TP6, TP7, TP8, TP9, TP10, TP11, TP12, TP13: TPB1,27; B1,27
U6: SAM4LC8BA; QFN-64-9MM
X2: 16MHz; FHXXX

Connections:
5V: JP3.1 (12); also elsewhere on the board
!FTDI_RTS: TP11.TP, U6.26 (PA08); also elsewhere on the board
!LIGHT_INT: TP10.TP, U6.51 (PA20); also elsewhere on the board
!NRF_RESET: U6.44 (PA17); also elsewhere on the board
!SAM4L_RESET: J2.3 (!RESET), JP4.11, S1.1, U6.4 (!RESET); also elsewhere on the board
ACC_INT1: TP8.TP, U6.29 (PA09); also elsewhere on the board
ACC_INT2: TP9.TP, U6.49 (PA18); also elsewhere on the board
ADVREFP: U6.24 (ADVREFP)
BLUE_LED: R1.1, U6.40 (PA13)
BUCK/LDO_N1: R9.2, U6.3 (PA02)
BUTTON: R12.1, S2.1, U6.43 (PA16)
FTDI_IN: TP13.TP, U6.32 (PA12); also elsewhere on the board
FTDI_OUT: TP12.TP, U6.31 (PA11); also elsewhere on the board
GND: C2.2, C3.2, C18.2, C19.2, C20.2, C21.2, C22.2, C25.2, J2.5 (GND), JP3.2 (11), JP4.9, R9.1, S1.2, S2.2, U6.6 (GND), U6.23 (GNDANA), U6.38 (GND), U6.64 (GND), U6.GND, X2.2 (GND), X2.4 (GND); also elsewhere on the board
GREEN_LED: R2.1, U6.41 (PA14)
unnamed: D1.3 (B), R2.2
unnamed: D1.4 (G), R3.2
unnamed: D1.2 (R), R1.2
unnamed: U6.36 (BIASH), U6.37 (BIASL)
unnamed: U6.33 (CAPH), U6.34 (CAPL)
unnamed: C18.1, FB1.1, U6.25 (VDDANA)
unnamed: C22.1, C25.1, U6.5 (VDDCORE), U6.7 (VDDOUT)
NRF_CTS: TP2.TP, U6.28 (PB07); also elsewhere on the board
NRF_IN: TP5.TP, U6.47 (PB10); also elsewhere on the board
NRF_INT: TP3.TP, U6.45 (PB08); also elsewhere on the board
NRF_OUT: TP4.TP, U6.46 (PB09); also elsewhere on the board
NRF_RTS: TP1.TP, U6.27 (PB06); also elsewhere on the board
PARTICLE_A0: JP3.12 (1), U6.15 (PA04)
PARTICLE_A1: JP3.11 (2), U6.16 (PA05)
PARTICLE_A2: JP3.10 (3), U6.13 (PB02)
PARTICLE_A3: JP3.9 (4), U6.14 (PB03)
PARTICLE_A4: JP3.8 (5), U6.19 (PB04)
PARTICLE_A5: JP3.7 (6), U6.20 (PB05)
PARTICLE_D0: JP4.1, U6.57 (PB14)
PARTICLE_D1: JP4.2, U6.58 (PB15)
PARTICLE_D2: JP4.3, U6.56 (PA22)
PARTICLE_D3: JP4.4, U6.55 (PA21)
PARTICLE_D4: JP4.5, U6.59 (PA23)
PARTICLE_D5: JP4.6, U6.60 (PA24)
PARTICLE_D6: JP4.7, U6.48 (PB11)
PARTICLE_D7: JP4.8, U6.53 (PB12)
PARTICLE_DAC: JP3.6 (7), U6.21 (PA06)
PARTICLE_RX: JP3.4 (9), U6.62 (PA25)
PARTICLE_TX: JP3.3 (10), U6.63 (PA26)
PARTICLE_WKP: JP3.5 (8), U6.22 (PA07)
RED_LED: R3.1, U6.42 (PA15)
SAM4L_SWDCLK: J2.4 (SWDCLK), R11.1, U6.9 (TCK)
SAM4L_SWDIO: J2.2 (SWDIO), R10.1, U6.10 (PA03)
SAM4L_XIN1: C2.1, U6.1 (PA00), X2.3 (2)
SAM4L_XOUT1: C3.1, U6.2 (PA01), X2.1
SENSORS_SCL: TP7.TP, U6.12 (PB01); also elsewhere on the board
SENSORS_SDA: TP6.TP, U6.11 (PB00); also elsewhere on the board
VCC: C19.1, C20.1, C21.1, D1.1 (VDD), FB1.2, J2.1 (VCC), JP4.12, R10.2, R11.2, R12.2, U6.8 (VDDIN), U6.35 (VLCD), U6.39 (VLCDIN), U6.52 (VDDIO), U6.61 (VDDIO); also elsewhere on the board

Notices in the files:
parts and their libraries:
SparkFun-Passives: Licensing: CC v3.0 Share-Alike You are welcome to use this library for commercial purposes.
